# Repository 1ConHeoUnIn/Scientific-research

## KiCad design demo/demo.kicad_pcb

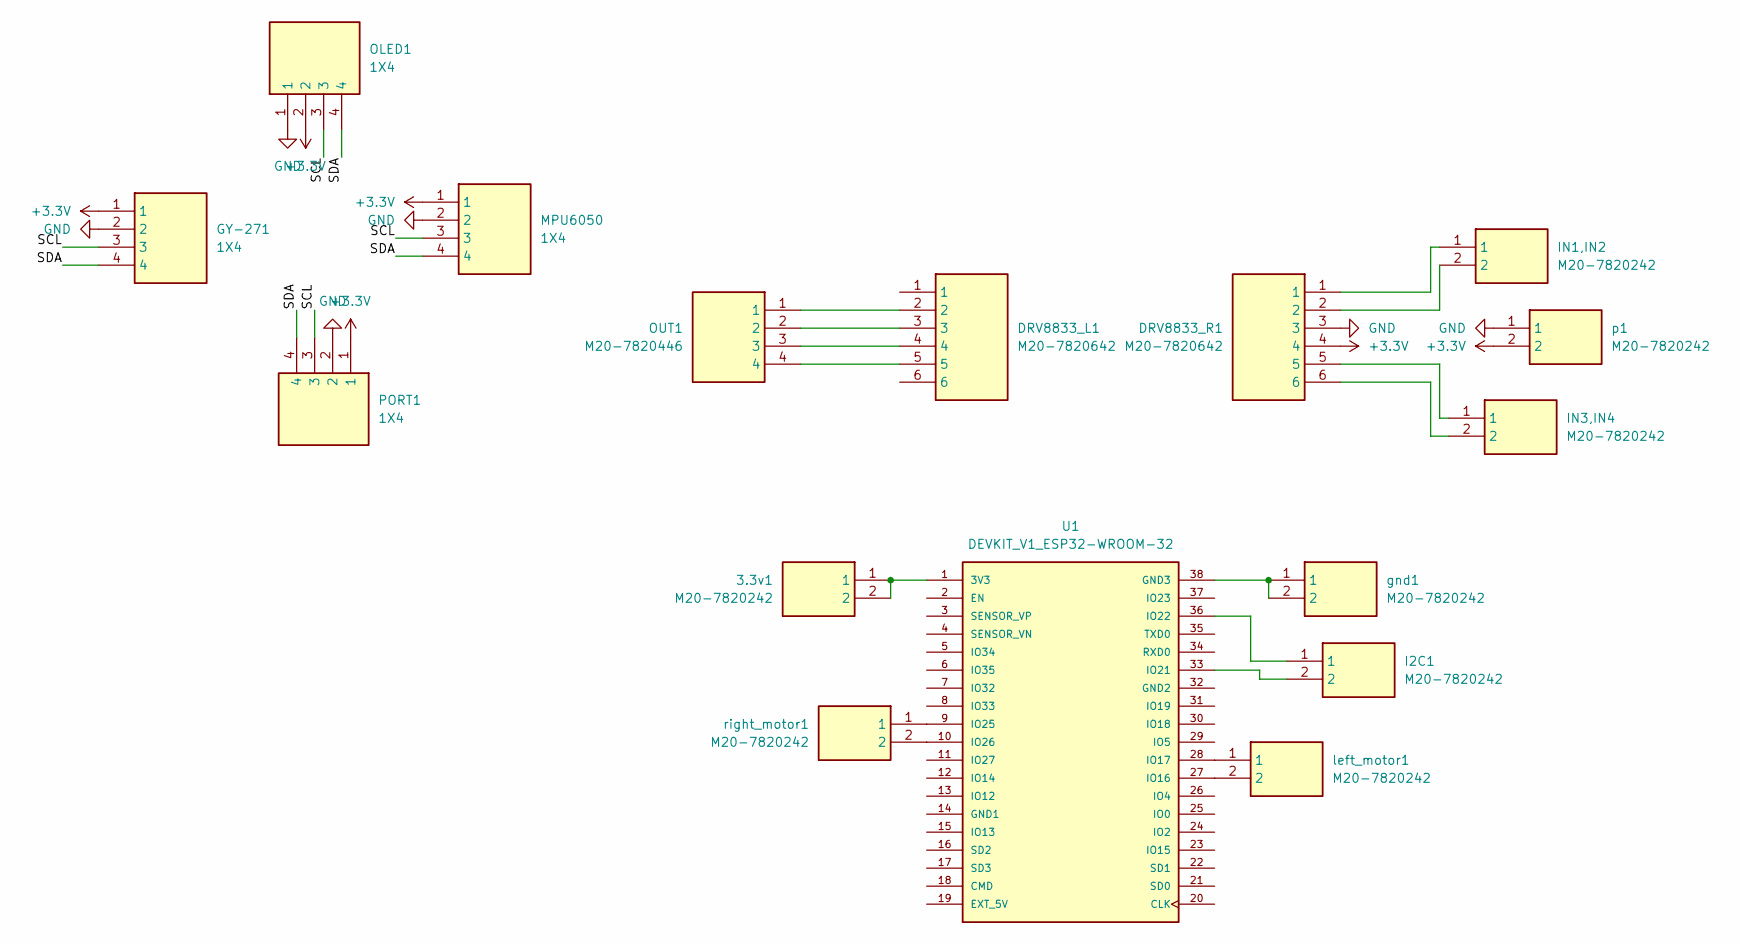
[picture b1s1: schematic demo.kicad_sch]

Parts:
3.3v1: M20-7820242; female_header_1x2; Manufacturer_Part_Number M20-7820242; Mouser Part Number 855-M20-7820242
DRV8833_L1, DRV8833_R1: M20-7820642; female_header_1x6; Manufacturer_Part_Number M20-7820642; Mouser Part Number 855-M20-7820642
GY-271: 1X4; RHDR4W70P0X254_1X4_1056X250X865P; Mouser Part Number 855-M20-7820446
I2C1: M20-7820242; female_header_1x2; Manufacturer_Part_Number M20-7820242; Mouser Part Number 855-M20-7820242
IN1,IN2, IN3,IN4: M20-7820242; female_header_1x2; Manufacturer_Part_Number M20-7820242; Mouser Part Number 855-M20-7820242
MPU6050: 1X4; RHDR4W70P0X254_1X4_1056X250X865P; Mouser Part Number 855-M20-7820446
OLED1: 1X4; RHDR4W70P0X254_1X4_1056X250X865P; Mouser Part Number 855-M20-7820446
OUT1: M20-7820446; RHDR4W70P0X254_1X4_1056X250X865P; Mouser Part Number 855-M20-7820446
PORT1: 1X4; RHDR4W70P0X254_1X4_1056X250X865P; Mouser Part Number 855-M20-7820446
U1: DEVKIT_V1_ESP32-WROOM-32; esp32_38; PARTREV N/A
gnd1: M20-7820242; female_header_1x2; Manufacturer_Part_Number M20-7820242; Mouser Part Number 855-M20-7820242
left_motor1: M20-7820242; female_header_1x2; Manufacturer_Part_Number M20-7820242; Mouser Part Number 855-M20-7820242
p1: M20-7820242; female_header_1x2; Manufacturer_Part_Number M20-7820242; Mouser Part Number 855-M20-7820242
right_motor1: M20-7820242; female_header_1x2; Manufacturer_Part_Number M20-7820242; Mouser Part Number 855-M20-7820242

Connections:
+3.3V: DRV8833_R1.4, GY-271.1, MPU6050.1, OLED1.2, PORT1.1, p1.2
/SCL: GY-271.3, MPU6050.3, OLED1.3, PORT1.3
/SDA: GY-271.4, MPU6050.4, OLED1.4, PORT1.4
GND: DRV8833_R1.3, GY-271.2, MPU6050.2, OLED1.1, PORT1.2, p1.1
unnamed: DRV8833_L1.2, OUT1.1
unnamed: DRV8833_L1.3, OUT1.2
unnamed: DRV8833_L1.4, OUT1.3
unnamed: DRV8833_L1.5, OUT1.4
unnamed: DRV8833_R1.1, IN1,IN2.1
unnamed: DRV8833_R1.2, IN1,IN2.2
unnamed: DRV8833_R1.5, IN3,IN4.1
unnamed: DRV8833_R1.6, IN3,IN4.2
unnamed: 3.3v1.1, 3.3v1.2, U1.1 (3V3)
unnamed: U1.38 (GND3), gnd1.1, gnd1.2
unnamed: U1.27 (IO16), left_motor1.2
unnamed: U1.28 (IO17), left_motor1.1
unnamed: I2C1.2, U1.33 (IO21)
unnamed: I2C1.1, U1.36 (IO22)
unnamed: U1.9 (IO25), right_motor1.1
unnamed: U1.10 (IO26), right_motor1.2

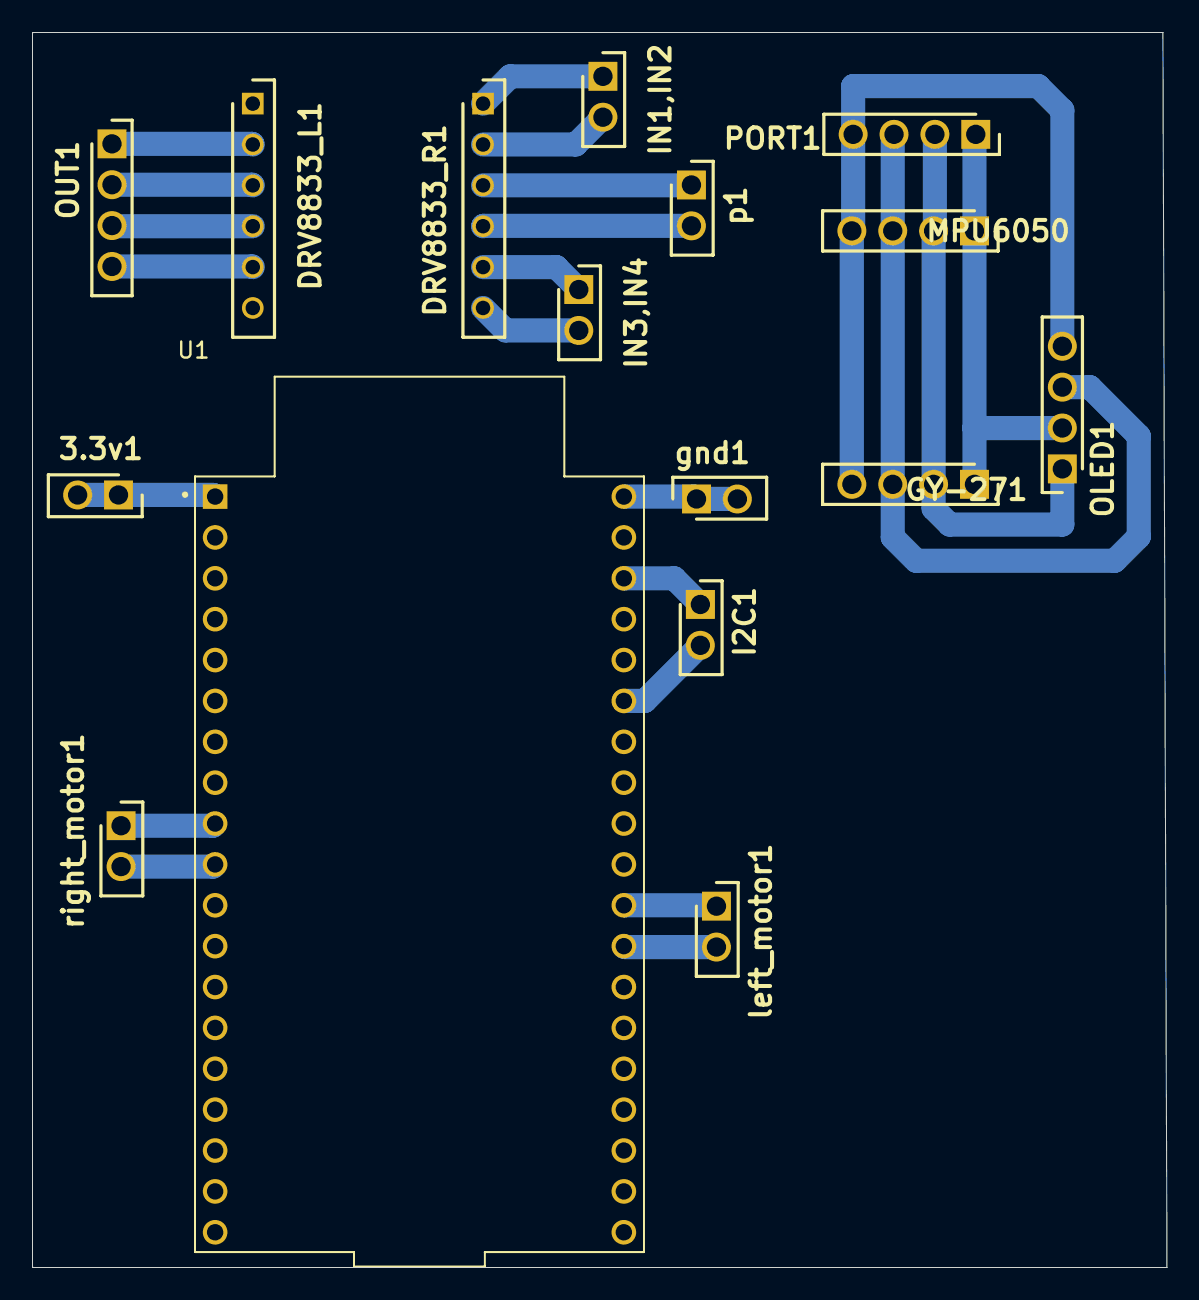
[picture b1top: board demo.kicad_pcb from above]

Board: 4 copper layers, 70.5 x 76.8 mm, 16 parts (0 on the bottom side), 20 nets.

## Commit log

2025-02-14 first
2025-03-09 encoder
2025-03-18 compass
2025-04-29 nearly finish
2025-04-29 delele file
2025-04-30 nhập được tọa độ, tàu di chuyển đến tọa độ, đọc khoảng cách còn sai
